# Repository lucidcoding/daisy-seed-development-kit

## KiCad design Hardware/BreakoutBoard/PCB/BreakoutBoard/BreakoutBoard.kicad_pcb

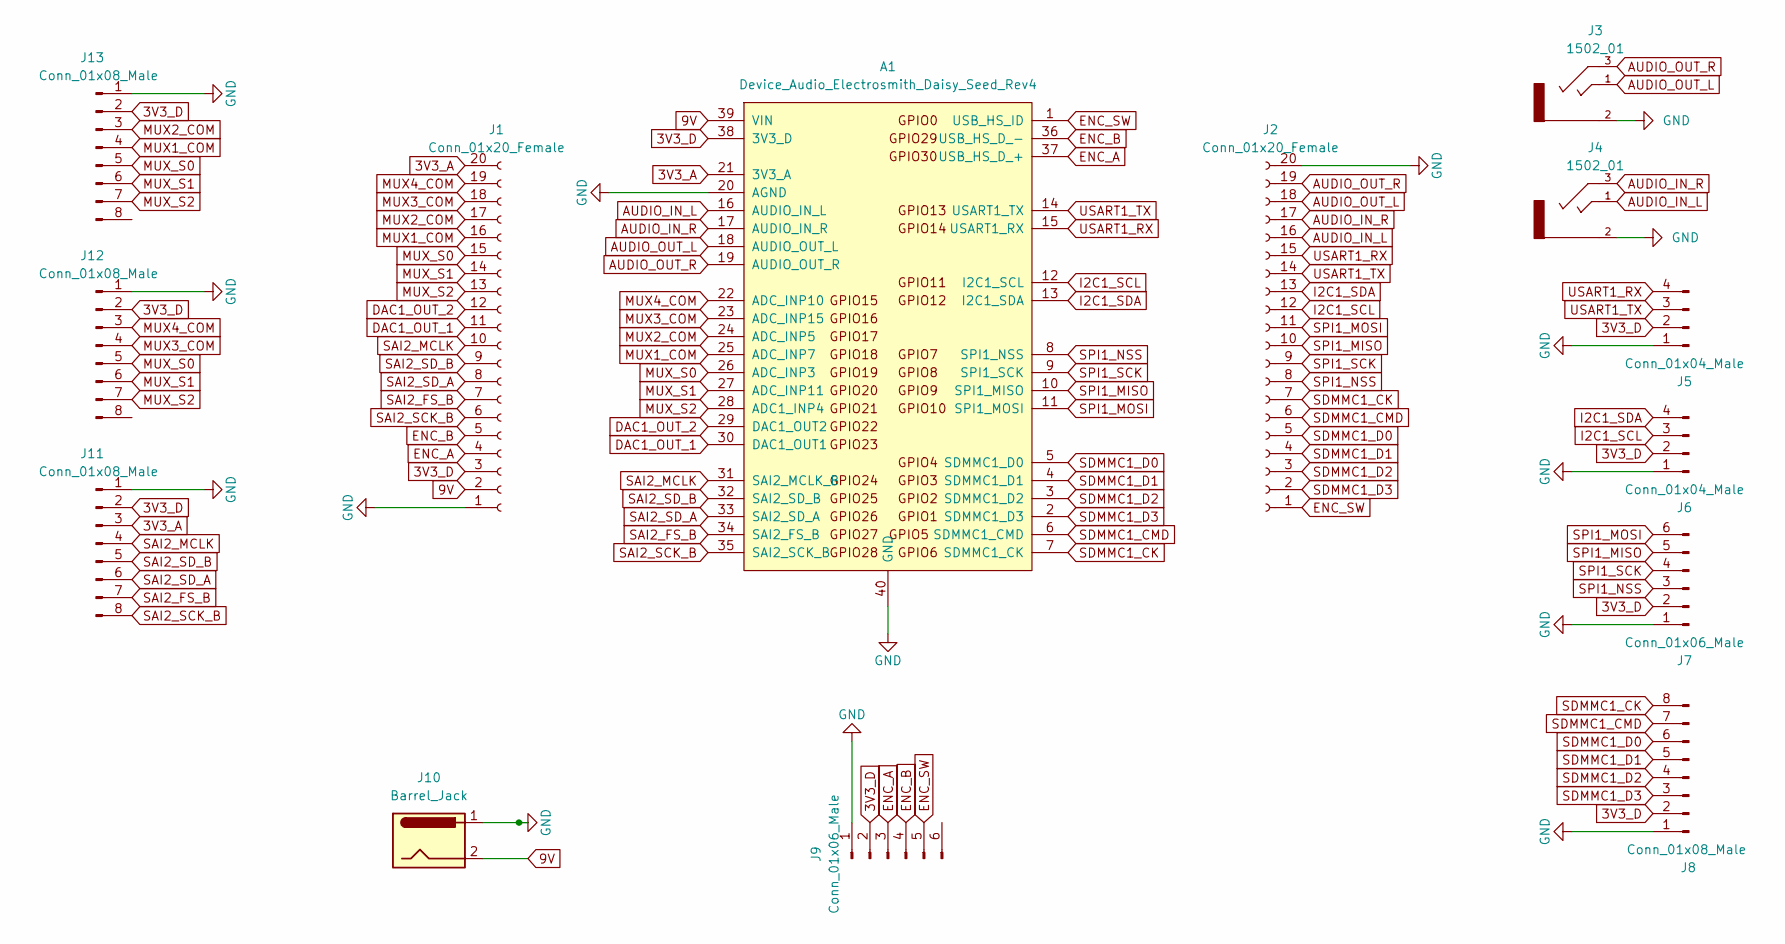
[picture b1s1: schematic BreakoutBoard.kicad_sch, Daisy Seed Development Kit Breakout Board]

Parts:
A1: Device_Audio_Electrosmith_Daisy_Seed_Rev4; Device_Audio_Electrosmith_Daisy_Seed
J1, J2: Conn_01x20_Female; PinSocket_1x20_P2.54mm_Vertical
J3, J4: 1502_01
J5, J6: Conn_01x04_Male; PinSocket_1x04_P2.54mm_Vertical
J7, J9: Conn_01x06_Male; PinSocket_1x06_P2.54mm_Vertical
J8, J11, J12, J13: Conn_01x08_Male; PinSocket_1x08_P2.54mm_Vertical
J10: Barrel_Jack; BarrelJack_GCT_DCJ200-10-A_Horizontal

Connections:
3V3_A: A1.21 (3V3_A), J1.20, J11.3
3V3_D: A1.38 (3V3_D), J1.3, J5.2, J6.2, J7.2, J8.2, J9.2, J11.2, J12.2, J13.2
9V: A1.39 (VIN), J1.2, J10.2
AUDIO_IN_L: A1.16 (AUDIO_IN_L), J2.16, J4.1
AUDIO_IN_R: A1.17 (AUDIO_IN_R), J2.17, J4.3
AUDIO_OUT_L: A1.18 (AUDIO_OUT_L), J2.18, J3.1
AUDIO_OUT_R: A1.19 (AUDIO_OUT_R), J2.19, J3.3
DAC1_OUT_1: A1.30 (DAC1_OUT1), J1.11
DAC1_OUT_2: A1.29 (DAC1_OUT2), J1.12
ENC_A: A1.37 (USB_HS_D_+), J1.4, J9.3
ENC_B: A1.36 (USB_HS_D_-), J1.5, J9.4
ENC_SW: A1.1 (USB_HS_ID), J2.1, J9.5
GND: A1.20 (AGND), A1.40 (GND), J1.1, J2.20, J3.2, J4.2, J5.1, J6.1, J7.1, J8.1, J9.1, J10.1, J11.1, J12.1, J13.1
I2C1_SCL: A1.12 (I2C1_SCL), J2.12, J6.3
I2C1_SDA: A1.13 (I2C1_SDA), J2.13, J6.4
MUX1_COM: A1.25 (ADC_INP7), J1.16, J13.4
MUX2_COM: A1.24 (ADC_INP5), J1.17, J13.3
MUX3_COM: A1.23 (ADC_INP15), J1.18, J12.4
MUX4_COM: A1.22 (ADC_INP10), J1.19, J12.3
MUX_S0: A1.26 (ADC_INP3), J1.15, J12.5, J13.5
MUX_S1: A1.27 (ADC_INP11), J1.14, J12.6, J13.6
MUX_S2: A1.28 (ADC1_INP4), J1.13, J12.7, J13.7
SAI2_FS_B: A1.34 (SAI2_FS_B), J1.7, J11.7
SAI2_MCLK: A1.31 (SAI2_MCLK_B), J1.10, J11.4
SAI2_SCK_B: A1.35 (SAI2_SCK_B), J1.6, J11.8
SAI2_SD_A: A1.33 (SAI2_SD_A), J1.8, J11.6
SAI2_SD_B: A1.32 (SAI2_SD_B), J1.9, J11.5
SDMMC1_CK: A1.7 (SDMMC1_CK), J2.7, J8.8
SDMMC1_CMD: A1.6 (SDMMC1_CMD), J2.6, J8.7
SDMMC1_D0: A1.5 (SDMMC1_D0), J2.5, J8.6
SDMMC1_D1: A1.4 (SDMMC1_D1), J2.4, J8.5
SDMMC1_D2: A1.3 (SDMMC1_D2), J2.3, J8.4
SDMMC1_D3: A1.2 (SDMMC1_D3), J2.2, J8.3
SPI1_MISO: A1.10 (SPI1_MISO), J2.10, J7.5
SPI1_MOSI: A1.11 (SPI1_MOSI), J2.11, J7.6
SPI1_NSS: A1.8 (SPI1_NSS), J2.8, J7.3
SPI1_SCK: A1.9 (SPI1_SCK), J2.9, J7.4
USART1_RX: A1.15 (USART1_RX), J2.15, J5.4
USART1_TX: A1.14 (USART1_TX), J2.14, J5.3

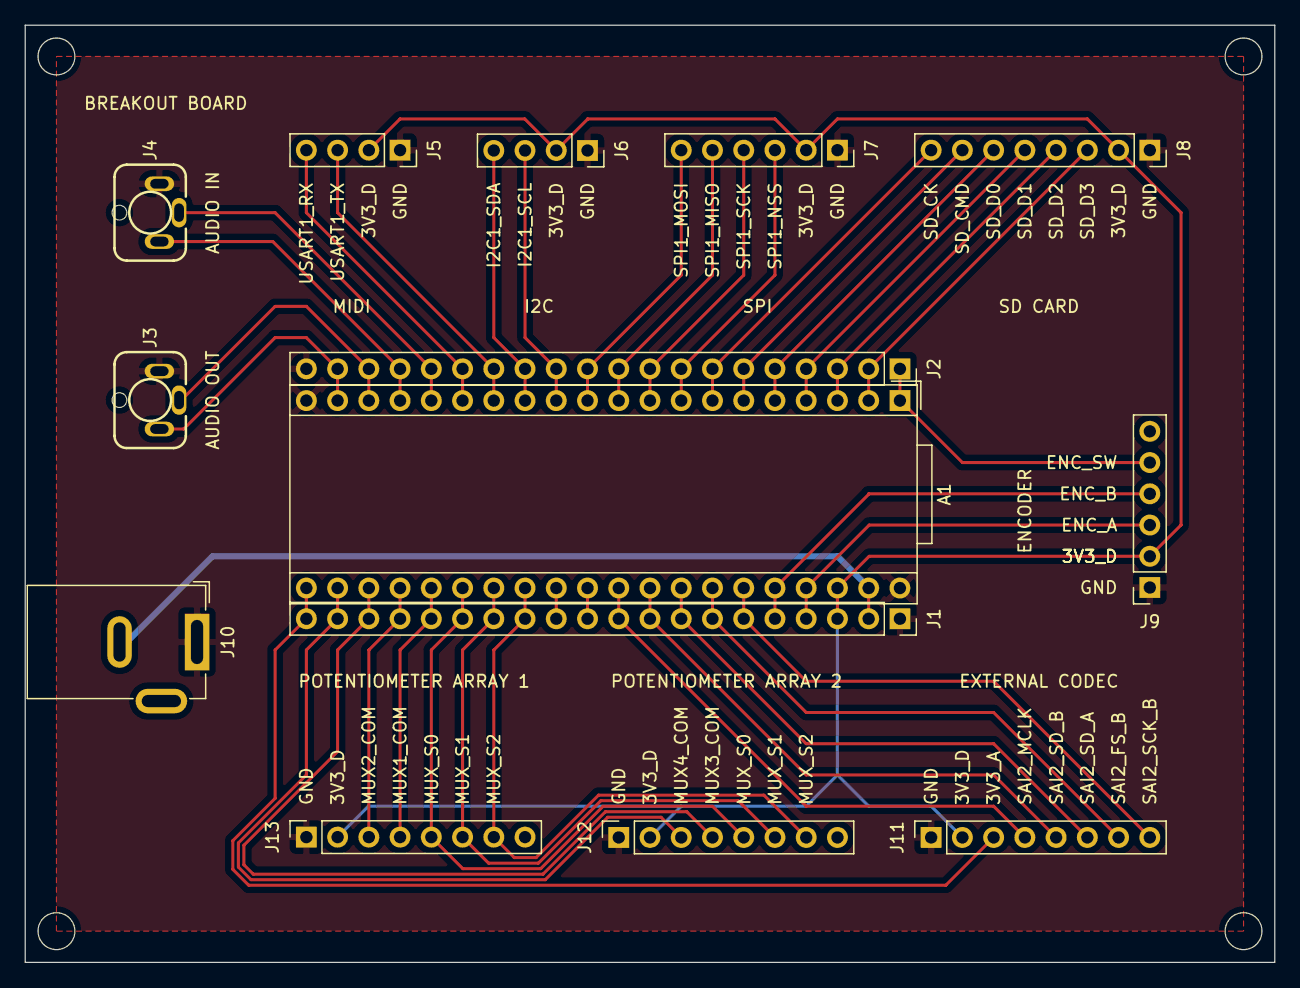
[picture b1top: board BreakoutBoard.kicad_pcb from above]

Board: 2 copper layers, 101.6 x 76.2 mm, 14 parts (0 on the bottom side), 39 nets.

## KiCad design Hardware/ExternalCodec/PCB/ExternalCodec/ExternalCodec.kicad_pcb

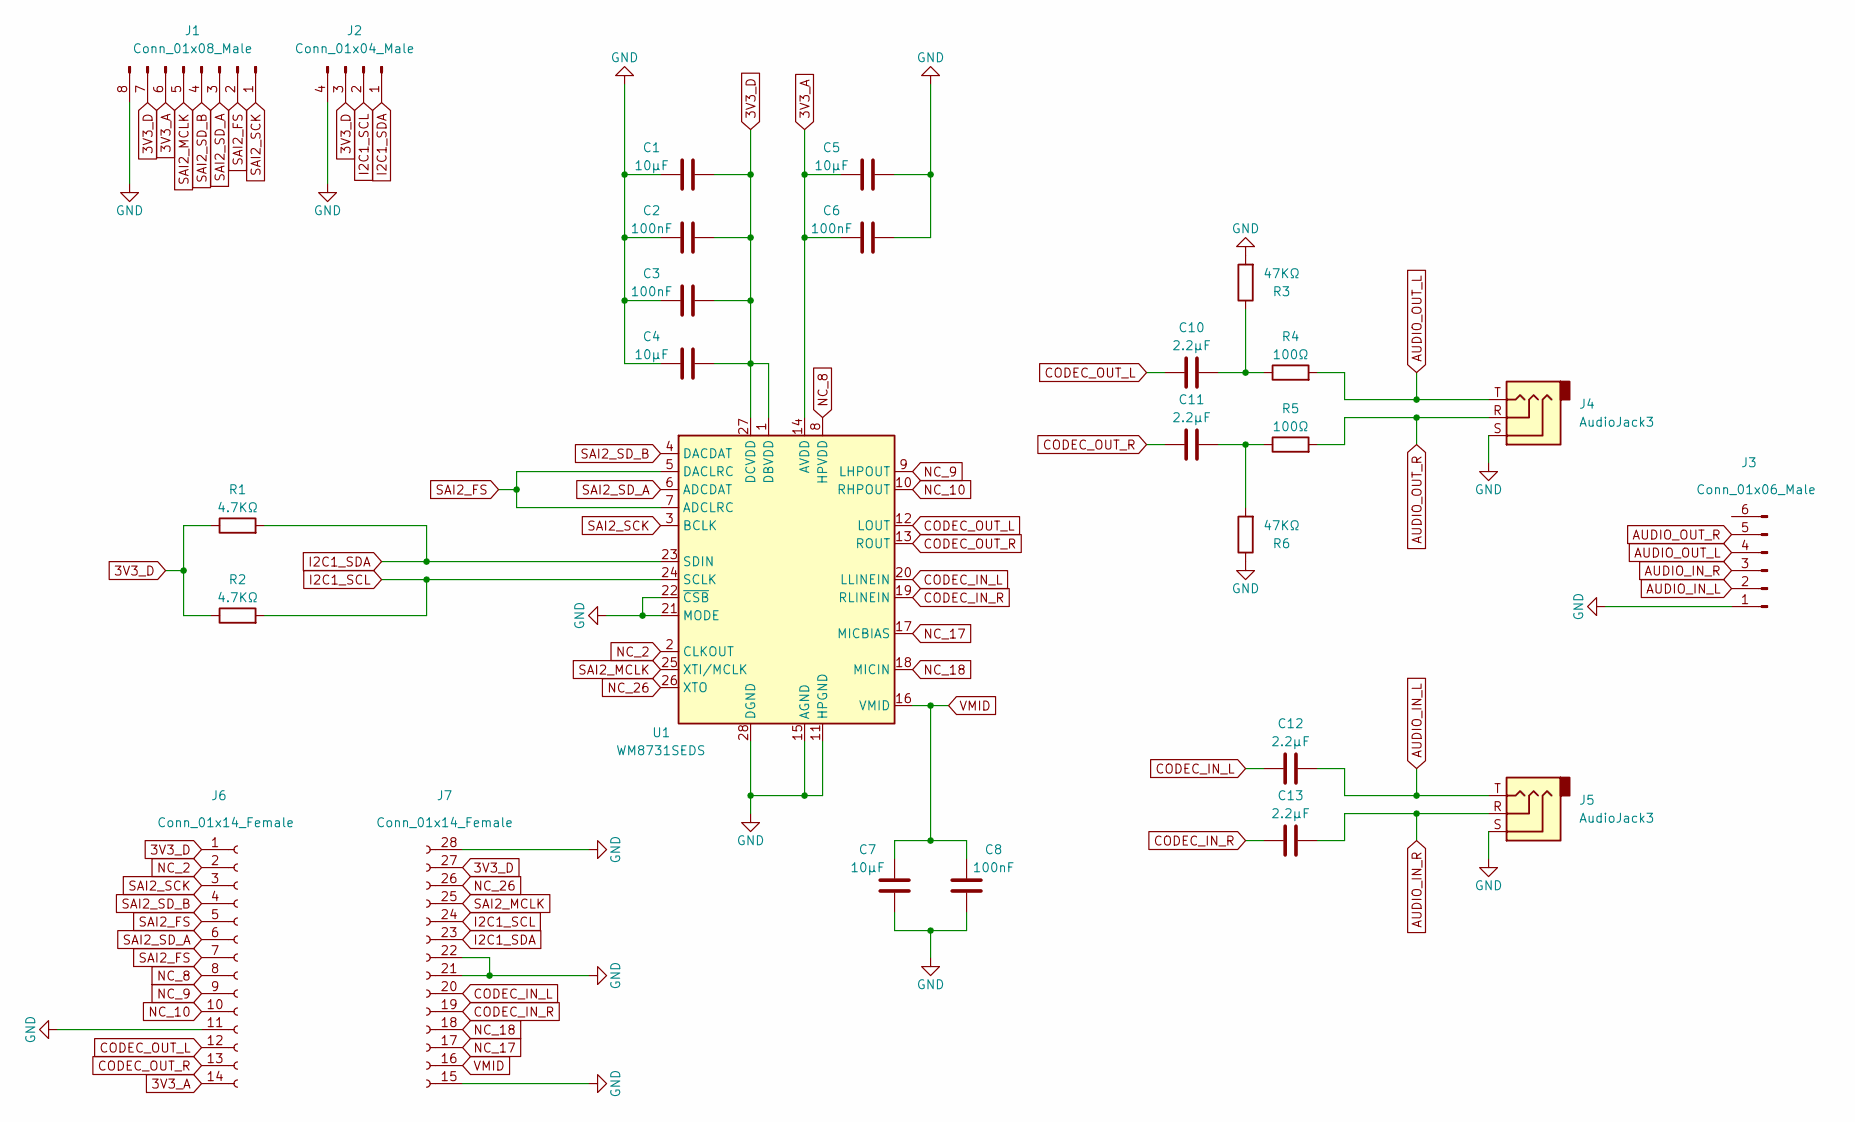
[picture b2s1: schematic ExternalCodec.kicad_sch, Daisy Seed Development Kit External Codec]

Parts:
C1, C4, C5, C7: 10μF; C_Disc_D5.0mm_W2.5mm_P5.00mm
C2, C3, C6, C8: 100nF; C_Disc_D5.0mm_W2.5mm_P2.50mm
C10, C11, C12, C13: 2.2μF; C_Disc_D5.0mm_W2.5mm_P5.00mm
J1: Conn_01x08_Male; PinSocket_1x08_P2.54mm_Vertical
J2: Conn_01x04_Male; PinSocket_1x04_P2.54mm_Vertical
J3: Conn_01x06_Male; PinSocket_1x06_P2.54mm_Vertical
J4, J5: AudioJack3; PJ-307
J6, J7: Conn_01x14_Female; PinSocket_1x14_P2.54mm_Vertical
R1, R2: 4.7KΩ; R_Axial_DIN0207_L6.3mm_D2.5mm_P10.16mm_Horizontal
R3, R6: 47KΩ; R_Axial_DIN0207_L6.3mm_D2.5mm_P10.16mm_Horizontal
R4, R5: 100Ω; R_Axial_DIN0207_L6.3mm_D2.5mm_P10.16mm_Horizontal
U1: WM8731SEDS; SSOP-28_5.3x10.2mm_P0.65mm

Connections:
3V3_A: C5.2, C6.2, J1.6, J6.14, U1.14 (AVDD)
3V3_D: C1.1, C2.1, C3.1, C4.1, J1.7, J2.3, J6.1, J7.27 (Pin_13), R1.1, R2.1, U1.1 (DBVDD), U1.27 (DCVDD)
AUDIO_IN_L: C12.2, J3.2, J5.T
AUDIO_IN_R: C13.2, J3.3, J5.R
AUDIO_OUT_L: J3.4, J4.T, R4.2
AUDIO_OUT_R: J3.5, J4.R, R5.2
CODEC_IN_L: C12.1, J7.20 (Pin_6), U1.20 (LLINEIN)
CODEC_IN_R: C13.1, J7.19 (Pin_5), U1.19 (RLINEIN)
CODEC_OUT_L: C10.1, J6.12, U1.12 (LOUT)
CODEC_OUT_R: C11.1, J6.13, U1.13 (ROUT)
GND: C1.2, C2.2, C3.2, C4.2, C5.1, C6.1, C7.1, C8.1, J1.8, J2.4, J3.1, J4.S, J5.S, J6.11, J7.15 (Pin_1), J7.21 (Pin_7), J7.22 (Pin_8), J7.28 (Pin_14), R3.2, R6.1, U1.11 (HPGND), U1.15 (AGND), U1.21 (MODE), U1.22 (~CSB), U1.28 (DGND)
I2C1_SCL: J2.2, J7.24 (Pin_10), R2.2, U1.24 (SCLK)
I2C1_SDA: J2.1, J7.23 (Pin_9), R1.2, U1.23 (SDIN)
NC_2: J6.2, U1.2 (CLKOUT)
NC_8: J6.8, U1.8 (HPVDD)
NC_9: J6.9, U1.9 (LHPOUT)
NC_10: J6.10, U1.10 (RHPOUT)
NC_17: J7.17 (Pin_3), U1.17 (MICBIAS)
NC_18: J7.18 (Pin_4), U1.18 (MICIN)
NC_26: J7.26 (Pin_12), U1.26 (XTO)
unnamed: C10.2, R3.1, R4.1
unnamed: C11.2, R5.1, R6.2
SAI2_FS: J1.2, J6.5, J6.7, U1.5 (DACLRC), U1.7 (ADCLRC)
SAI2_MCLK: J1.5, J7.25 (Pin_11), U1.25 (XTI/MCLK)
SAI2_SCK: J1.1, J6.3, U1.3 (BCLK)
SAI2_SD_A: J1.3, J6.6, U1.6 (ADCDAT)
SAI2_SD_B: J1.4, J6.4, U1.4 (DACDAT)
VMID: C7.2, C8.2, J7.16 (Pin_2), U1.16 (VMID)

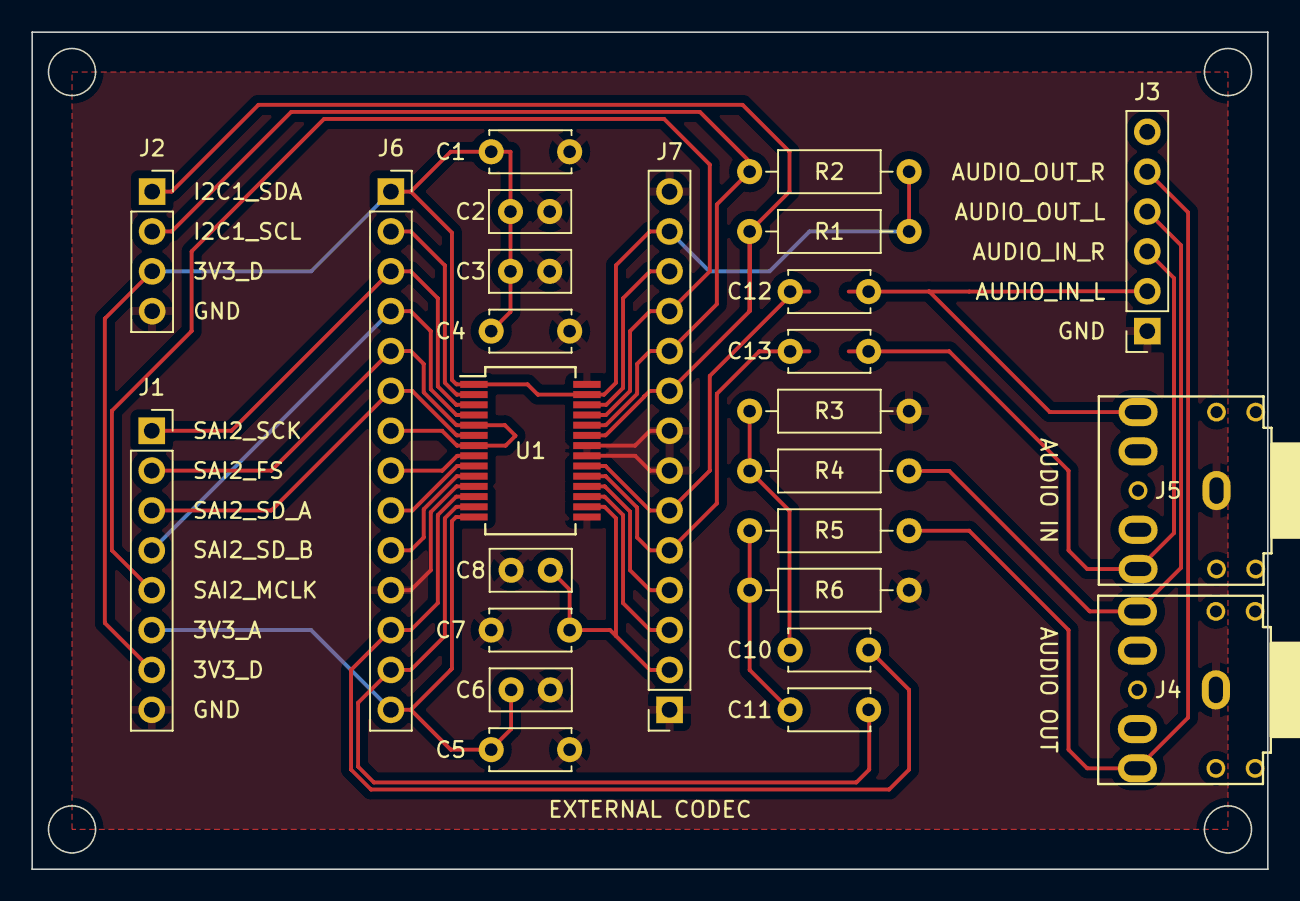
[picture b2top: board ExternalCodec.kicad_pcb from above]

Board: 2 copper layers, 78.7 x 53.3 mm, 26 parts (0 on the bottom side), 28 nets.

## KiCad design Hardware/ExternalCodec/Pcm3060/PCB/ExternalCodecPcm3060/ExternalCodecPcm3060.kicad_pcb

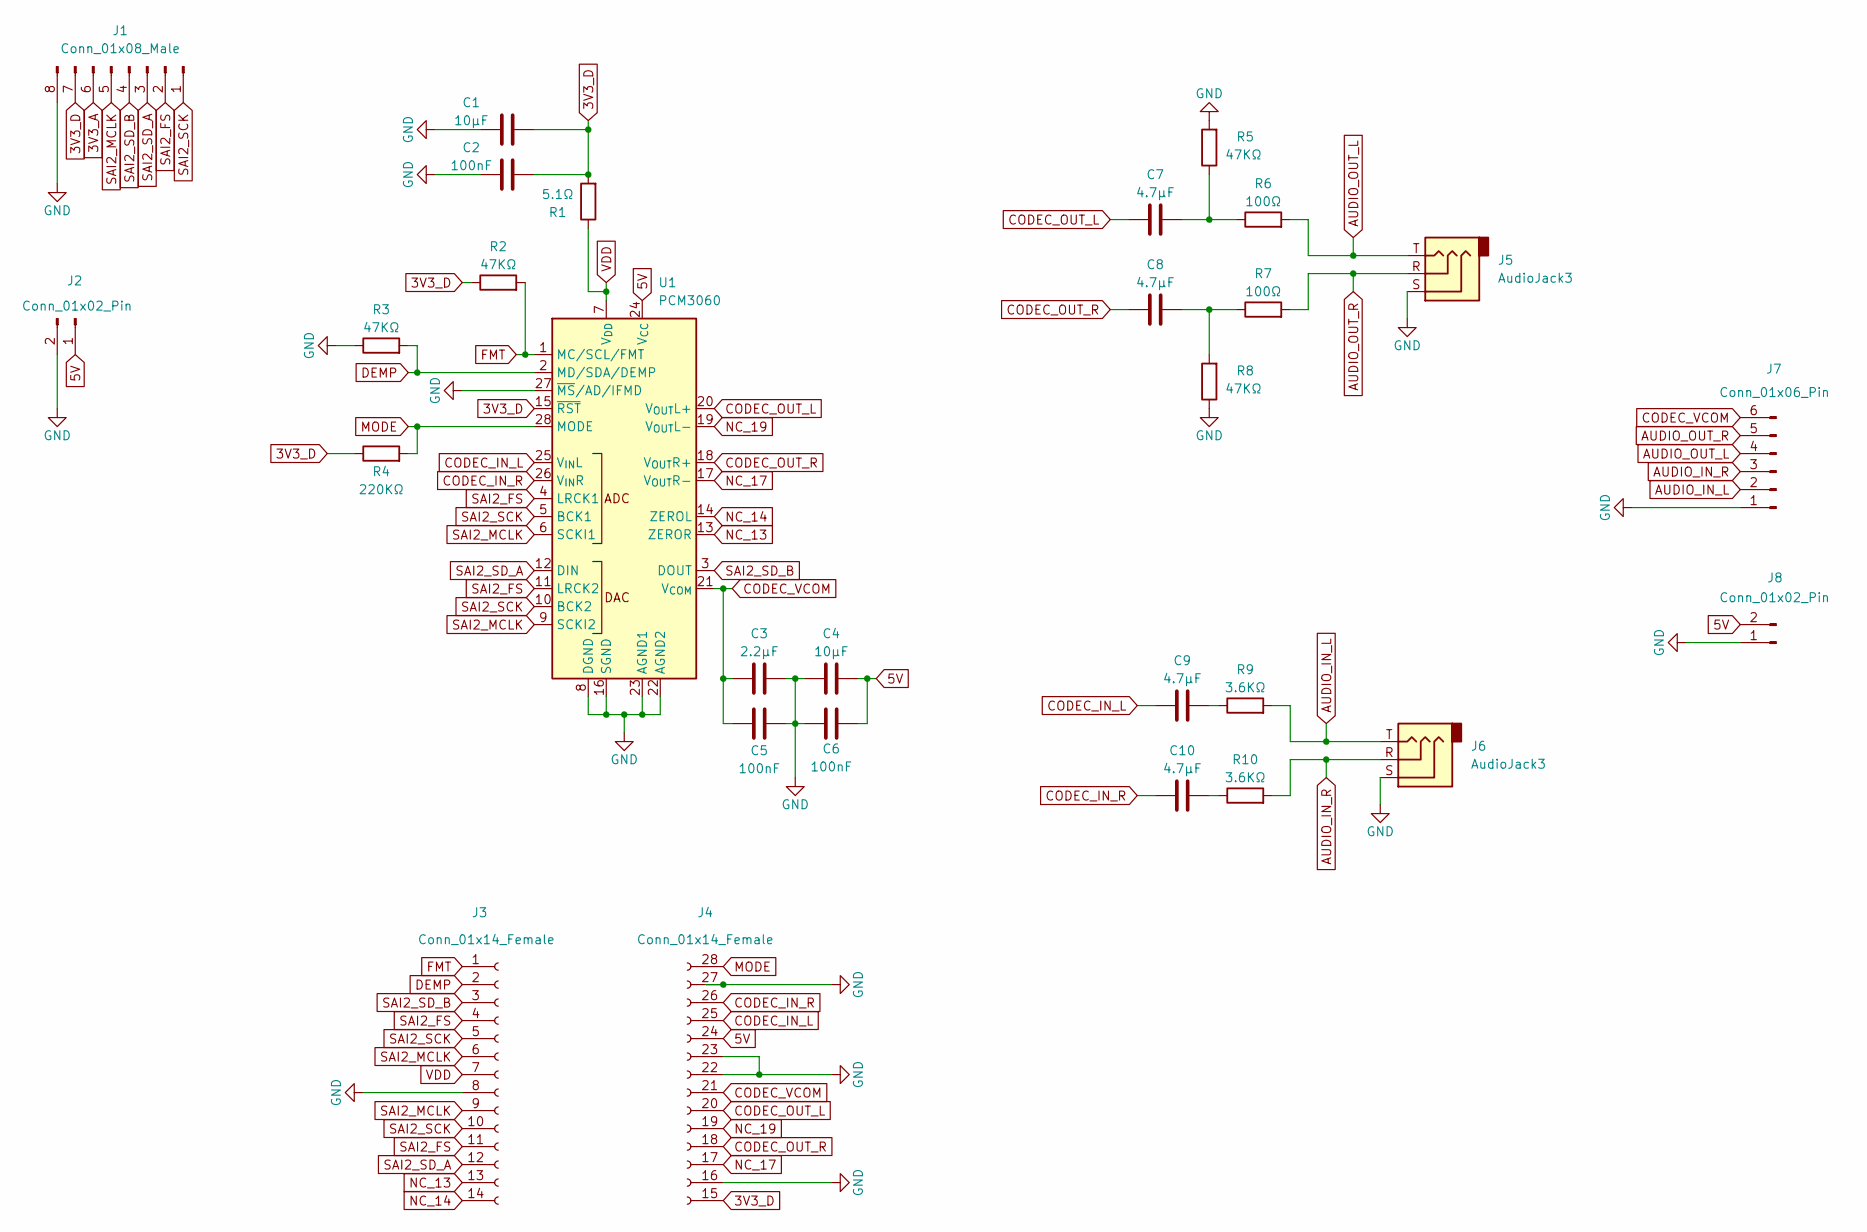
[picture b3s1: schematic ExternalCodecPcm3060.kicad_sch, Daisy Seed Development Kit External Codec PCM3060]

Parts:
C1, C4: 10μF; C_Disc_D5.0mm_W2.5mm_P5.00mm
C2, C5, C6: 100nF; C_Disc_D5.0mm_W2.5mm_P2.50mm
C3: 2.2μF; C_Disc_D5.0mm_W2.5mm_P5.00mm
C7, C8, C9, C10: 4.7μF; C_Disc_D5.0mm_W2.5mm_P5.00mm
J1: Conn_01x08_Male; PinSocket_1x08_P2.54mm_Vertical
J2, J8: Conn_01x02_Pin; PinSocket_1x02_P2.54mm_Vertical
J3, J4: Conn_01x14_Female; PinSocket_1x14_P2.54mm_Vertical
J5, J6: AudioJack3; PJ-307
J7: Conn_01x06_Pin; PinSocket_1x06_P2.54mm_Vertical
R1: 5.1Ω; R_Axial_DIN0207_L6.3mm_D2.5mm_P10.16mm_Horizontal
R2, R3, R5, R8: 47KΩ; R_Axial_DIN0207_L6.3mm_D2.5mm_P10.16mm_Horizontal
R4: 220KΩ; R_Axial_DIN0207_L6.3mm_D2.5mm_P10.16mm_Horizontal
R6, R7: 100Ω; R_Axial_DIN0207_L6.3mm_D2.5mm_P10.16mm_Horizontal
R9, R10: 3.6KΩ; R_Axial_DIN0207_L6.3mm_D2.5mm_P10.16mm_Horizontal
U1: PCM3060; TSSOP-28_4.4x9.7mm_P0.65mm

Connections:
3V3_A: J1.6
3V3_D: C1.1, C2.1, J1.7, J4.15 (Pin_1), R1.2, R2.1, R4.1, U1.15 (~RST)
5V: C4.2, C6.2, J2.1, J4.24 (Pin_10), J8.2, U1.24 (V_{CC})
AUDIO_IN_L: J6.T, J7.2, R9.2
AUDIO_IN_R: J6.R, J7.3, R10.2
AUDIO_OUT_L: J5.T, J7.4, R6.2
AUDIO_OUT_R: J5.R, J7.5, R7.2
CODEC_IN_L: C9.1, J4.25 (Pin_11), U1.25 (V_{IN}L)
CODEC_IN_R: C10.1, J4.26 (Pin_12), U1.26 (V_{IN}R)
CODEC_OUT_L: C7.1, J4.20 (Pin_6), U1.20 (V_{OUT}L+)
CODEC_OUT_R: C8.1, J4.18 (Pin_4), U1.18 (V_{OUT}R+)
CODEC_VCOM: C3.1, C5.1, J4.21 (Pin_7), J7.6, U1.21 (V_{COM})
DEMP: J3.2, R3.2, U1.2 (MD/SDA/DEMP)
FMT: J3.1, R2.2, U1.1 (MC/SCL/FMT)
GND: C1.2, C2.2, C3.2, C4.1, C5.2, C6.1, J1.8, J2.2, J3.8, J4.16 (Pin_2), J4.22 (Pin_8), J4.23 (Pin_9), J4.27 (Pin_13), J5.S, J6.S, J7.1, J8.1, R3.1, R5.2, R8.1, U1.8 (DGND), U1.16 (SGND), U1.22 (AGND2), U1.23 (AGND1), U1.27 (~MS/AD/IFMD)
MODE: J4.28 (Pin_14), R4.2, U1.28 (MODE)
NC_13: J3.13, U1.13 (ZEROR)
NC_14: J3.14, U1.14 (ZEROL)
NC_17: J4.17 (Pin_3), U1.17 (V_{OUT}R-)
NC_19: J4.19 (Pin_5), U1.19 (V_{OUT}L-)
unnamed: C7.2, R5.1, R6.1
unnamed: C8.2, R7.1, R8.2
unnamed: C9.2, R9.1
unnamed: C10.2, R10.1
SAI2_FS: J1.2, J3.4, J3.11, U1.4 (LRCK1), U1.11 (LRCK2)
SAI2_MCLK: J1.5, J3.6, J3.9, U1.6 (SCKI1), U1.9 (SCKI2)
SAI2_SCK: J1.1, J3.5, J3.10, U1.5 (BCK1), U1.10 (BCK2)
SAI2_SD_A: J1.3, J3.12, U1.12 (DIN)
SAI2_SD_B: J1.4, J3.3, U1.3 (DOUT)
VDD: J3.7, R1.1, U1.7 (V_{DD})

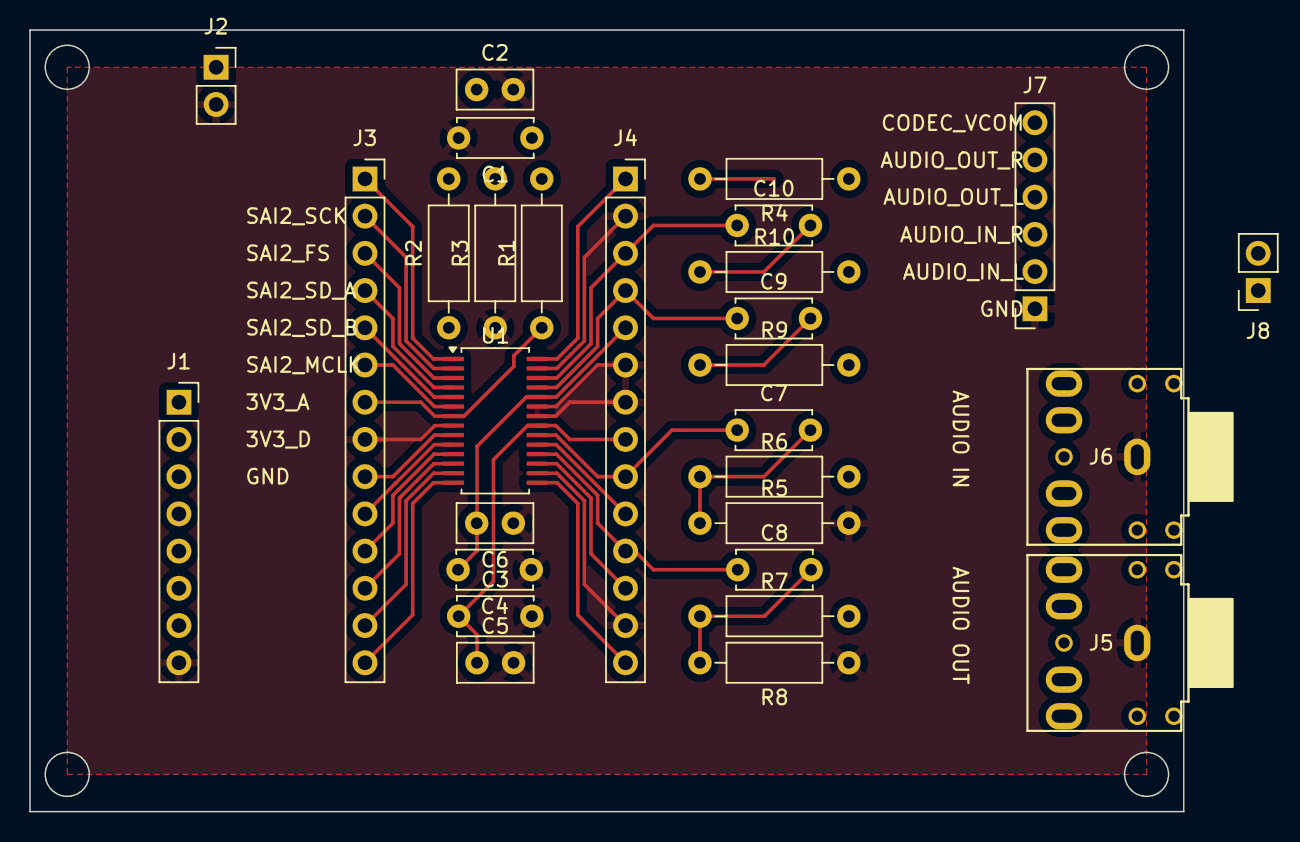
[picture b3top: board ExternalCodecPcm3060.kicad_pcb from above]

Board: 2 copper layers, 78.7 x 53.3 mm, 29 parts (0 on the bottom side), 29 nets.

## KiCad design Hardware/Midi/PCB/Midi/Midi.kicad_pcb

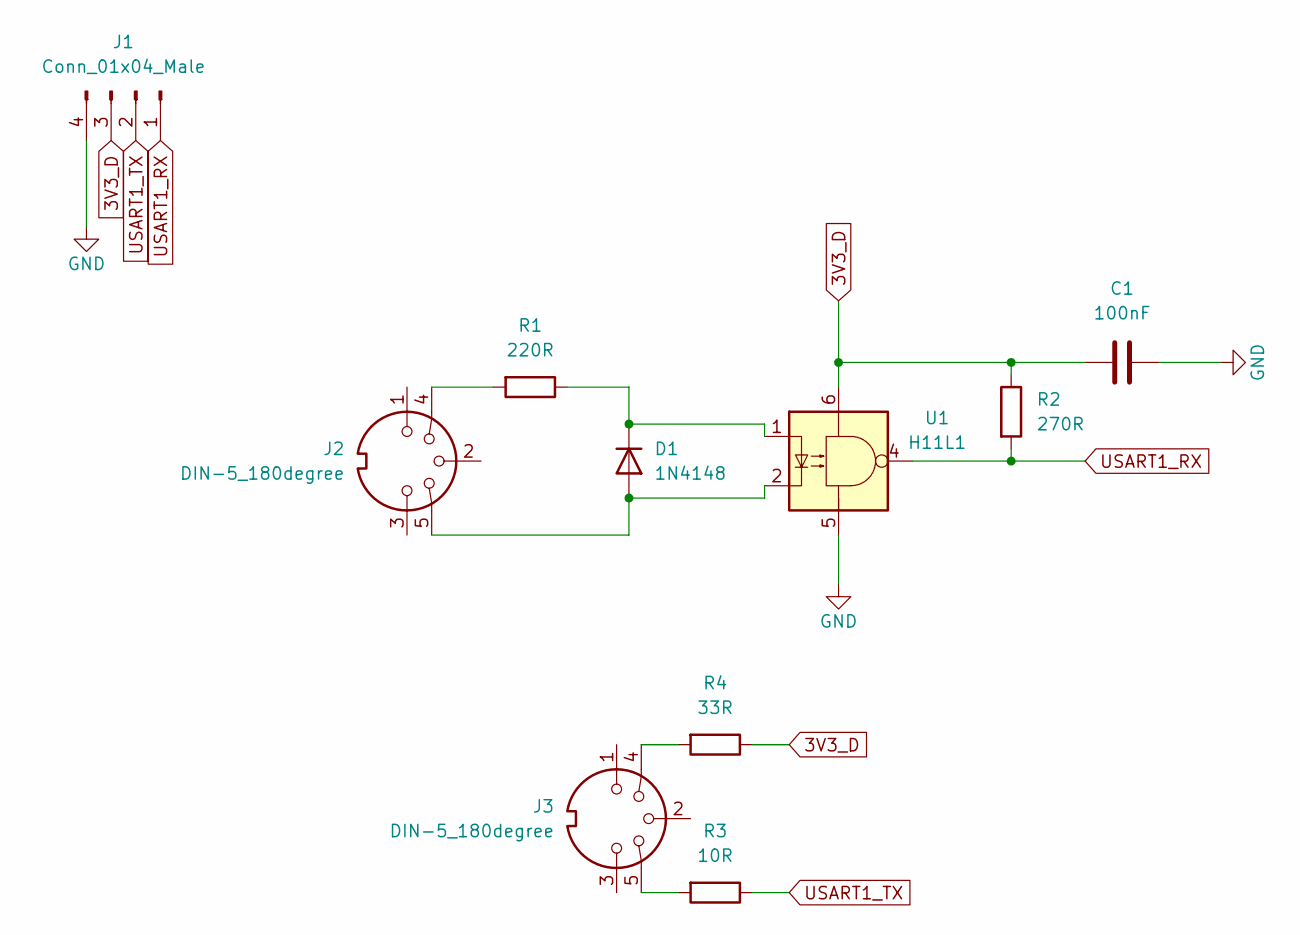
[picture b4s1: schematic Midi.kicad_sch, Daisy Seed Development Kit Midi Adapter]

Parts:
C1: 100nF; C_Disc_D5.0mm_W2.5mm_P2.50mm
D1: 1N4148; D_DO-35_SOD27_P10.16mm_Horizontal
J1: Conn_01x04_Male; PinSocket_1x04_P2.54mm_Vertical
J2, J3: DIN-5_180degree; MIDI_DIN5
R1: 220R; R_Axial_DIN0207_L6.3mm_D2.5mm_P10.16mm_Horizontal
R2: 270R; R_Axial_DIN0207_L6.3mm_D2.5mm_P10.16mm_Horizontal
R3: 10R; R_Axial_DIN0207_L6.3mm_D2.5mm_P10.16mm_Horizontal
R4: 33R; R_Axial_DIN0207_L6.3mm_D2.5mm_P10.16mm_Horizontal
U1: H11L1; DIP-6_W7.62mm_Socket

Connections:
3V3_D: C1.1, J1.3, R2.1, R4.1, U1.6
GND: C1.2, J1.4, U1.5
unnamed: D1.1 (K), R1.1, U1.1
unnamed: J2.4, R1.2
unnamed: J3.5, R3.2
unnamed: J3.4, R4.2
unnamed: D1.2 (A), J2.5, U1.2
USART1_RX: J1.1, R2.2, U1.4
USART1_TX: J1.2, R3.1

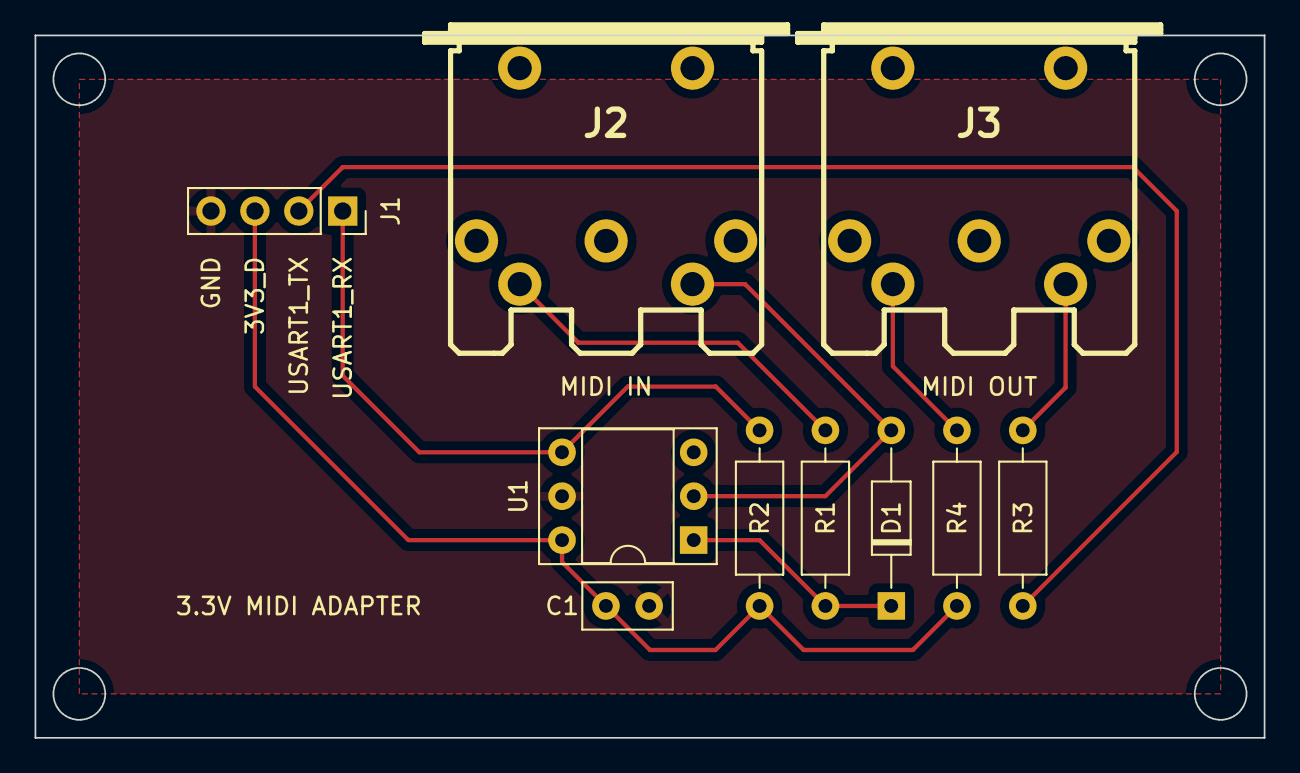
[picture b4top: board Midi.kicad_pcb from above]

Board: 2 copper layers, 71.1 x 40.6 mm, 10 parts (0 on the bottom side), 9 nets.

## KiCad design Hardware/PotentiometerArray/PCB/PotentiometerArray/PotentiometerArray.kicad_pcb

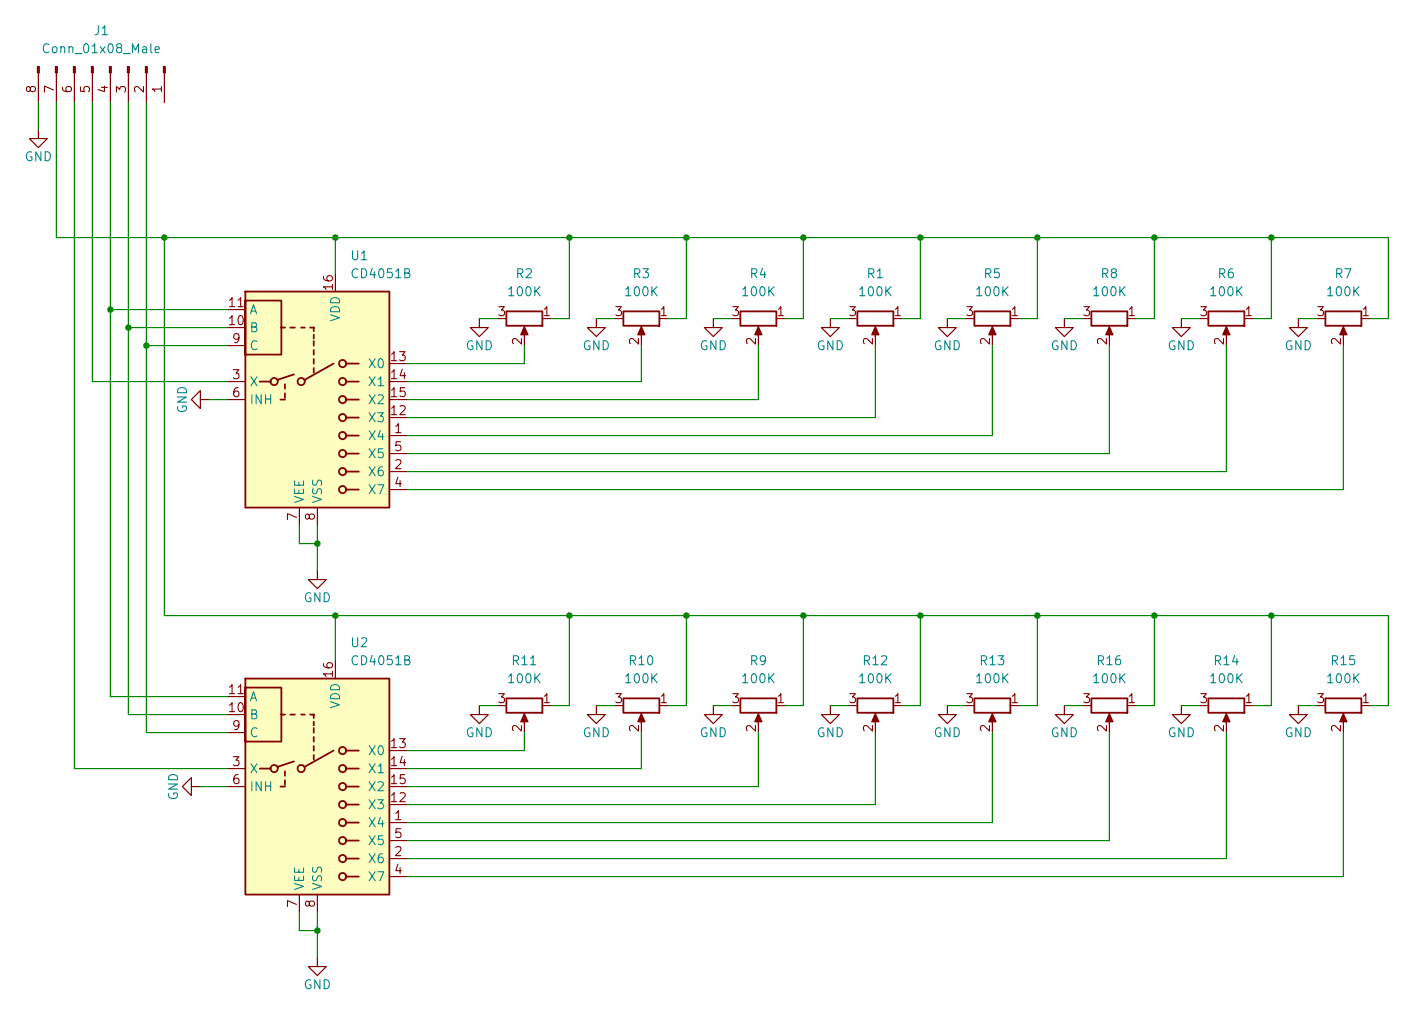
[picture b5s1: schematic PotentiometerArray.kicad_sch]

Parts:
J1: Conn_01x08_Male; PinSocket_1x08_P2.54mm_Vertical
R1, R2, R3, R4, R5, R6, R7, R8, R9, R10, R11, R12, R13, R14, R15, R16: 100K; Potentiometer_Bourns_PTV09A-1_Single_Vertical
U1, U2: CD4051B; DIP-16_W7.62mm

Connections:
GND: J1.8, R1.3, R2.3, R3.3, R4.3, R5.3, R6.3, R7.3, R8.3, R9.3, R10.3, R11.3, R12.3, R13.3, R14.3, R15.3, R16.3, U1.6 (INH), U1.7 (VEE), U1.8 (VSS), U2.6 (INH), U2.7 (VEE), U2.8 (VSS)
unnamed: J1.2, U1.9 (C), U2.9 (C)
unnamed: J1.3, U1.10 (B), U2.10 (B)
unnamed: J1.4, U1.11 (A), U2.11 (A)
unnamed: J1.5, U1.3 (X)
unnamed: J1.6, U2.3 (X)
unnamed: J1.7, R1.1, R2.1, R3.1, R4.1, R5.1, R6.1, R7.1, R8.1, R9.1, R10.1, R11.1, R12.1, R13.1, R14.1, R15.1, R16.1, U1.16 (VDD), U2.16 (VDD)
unnamed: R1.2, U1.12 (X3)
unnamed: R2.2, U1.13 (X0)
unnamed: R3.2, U1.14 (X1)
unnamed: R4.2, U1.15 (X2)
unnamed: R5.2, U1.1 (X4)
unnamed: R6.2, U1.2 (X6)
unnamed: R7.2, U1.4 (X7)
unnamed: R8.2, U1.5 (X5)
unnamed: R9.2, U2.15 (X2)
unnamed: R10.2, U2.14 (X1)
unnamed: R11.2, U2.13 (X0)
unnamed: R12.2, U2.12 (X3)
unnamed: R13.2, U2.1 (X4)
unnamed: R14.2, U2.2 (X6)
unnamed: R15.2, U2.4 (X7)
unnamed: R16.2, U2.5 (X5)

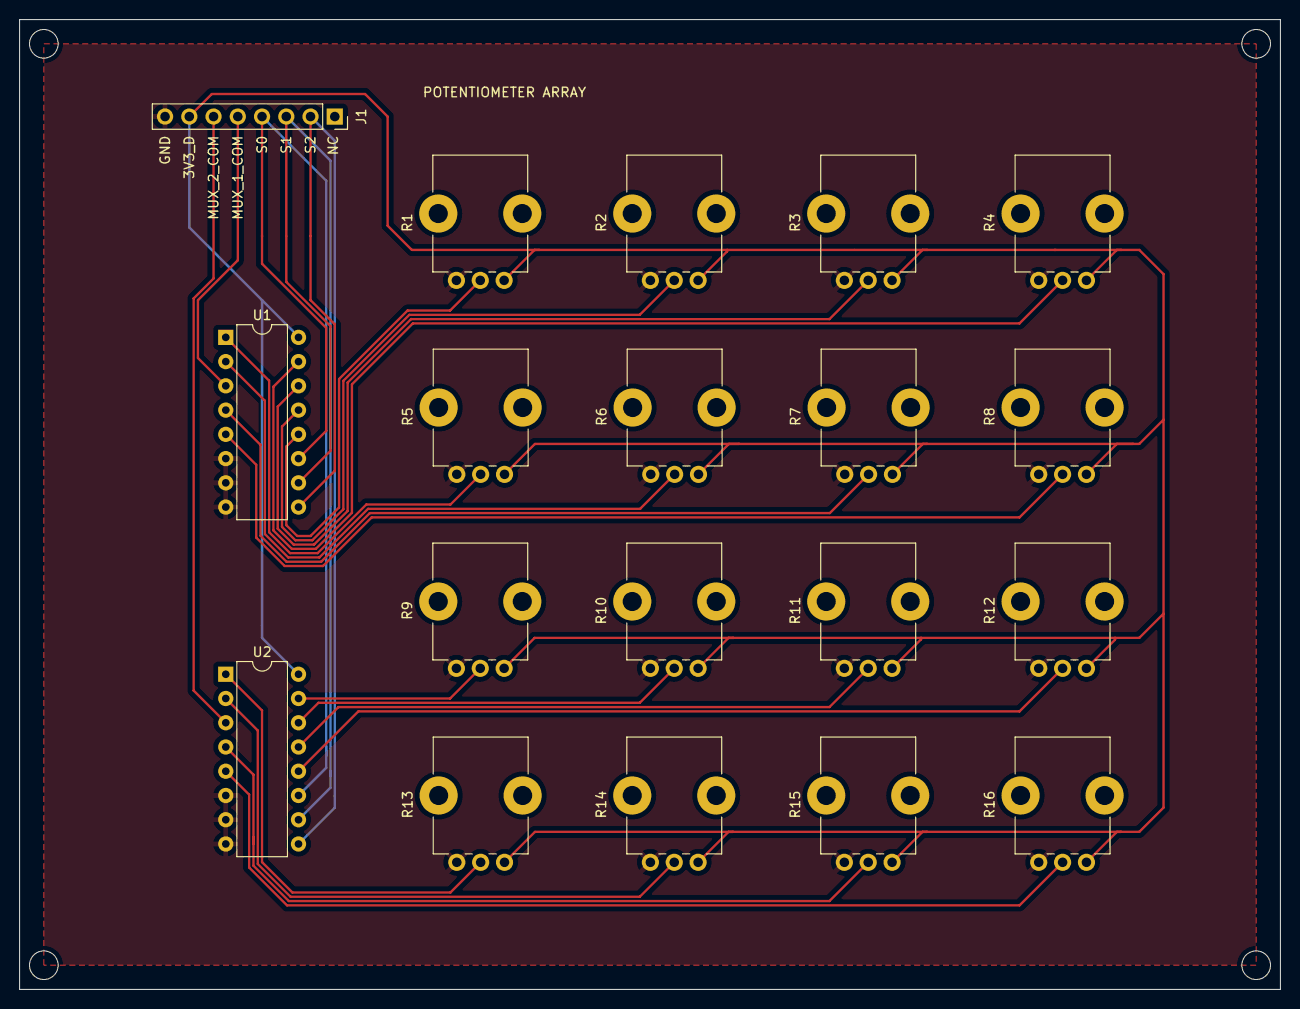
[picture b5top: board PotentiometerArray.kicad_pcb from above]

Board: 2 copper layers, 132.1 x 101.6 mm, 19 parts (0 on the bottom side), 23 nets.
